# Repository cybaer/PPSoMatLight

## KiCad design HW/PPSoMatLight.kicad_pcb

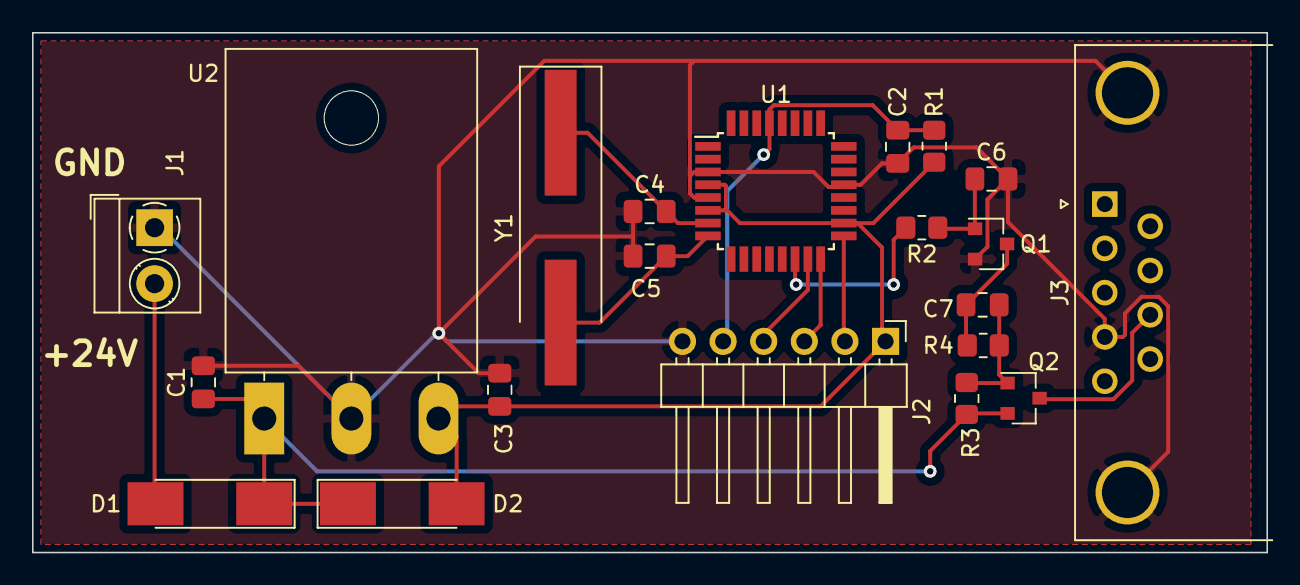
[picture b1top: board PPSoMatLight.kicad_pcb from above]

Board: 2 copper layers, 77.2 x 32.5 mm, 21 parts (0 on the bottom side), 15 nets.

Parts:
C1: 330nF; C_0805_2012Metric_Pad1.18x1.45mm_HandSolder
C2, C3: 100nF; C_0805_2012Metric_Pad1.18x1.45mm_HandSolder
C4, C5: 22pF; C_0805_2012Metric_Pad1.18x1.45mm_HandSolder
C6: 1n; C_0805_2012Metric_Pad1.18x1.45mm_HandSolder
C7: 10n; C_0805_2012Metric_Pad1.18x1.45mm_HandSolder
D1, D2: 1N4002; D_MELF_Handsoldering
J1: Conn_01x02; TerminalBlock_MetzConnect_Type059_RT06302HBWC_1x02_P3.50mm_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
J2: Conn_01x06; PinHeader_1x06_P2.54mm_Horizontal
J3: DB9_Female_MountingHoles; DSUB-9_Female_Horizontal_P2.77x2.84mm_EdgePinOffset7.70mm_H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
Q1: BC817; SOT-23
Q2: BC807; SOT-23
R1, R4: 10K; R_0805_2012Metric_Pad1.20x1.40mm_HandSolder
R2: 100K; R_0805_2012Metric_Pad1.20x1.40mm_HandSolder
R3: 1M; R_0805_2012Metric_Pad1.20x1.40mm_HandSolder
U1: ATmega328P-AU; TQFP-32_7x7mm_P0.8mm
U2: L7805; TO-3P-3_Horizontal_TabDown
Y1: Crystal; Crystal_SMD_HC49-SD_HandSoldering

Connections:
+5V: C3.1, D2.2, J2.1, R1.1, U1.4, U1.6, U1.18, U2.3
+24V: C1.1, D1.1, D2.1, Q2.2, R3.2, U2.1
GND: C1.2, C2.2, C3.2, C4.1, C5.1, C6.2, J1.1, J2.6, J3.0, J3.4, Q1.2, U1.3, U1.5, U1.21, U2.2
MISO: J2.3, U1.16
MOSI: J2.4, U1.15
unnamed: C4.2, U1.7, Y1.1
unnamed: C5.2, U1.8, Y1.2
unnamed: C6.1, Q1.1, R2.1
unnamed: C7.1, Q2.1, R3.1, R4.2
unnamed: C7.2, Q1.3, R4.1
unnamed: D1.2, J1.2
unnamed: J3.8, Q2.3
unnamed: R2.2, U1.14
RST: C2.1, J2.5, R1.2, U1.29
SCK: J2.2, U1.17

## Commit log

2021-02-11 First release
2021-02-11 PDFs added
